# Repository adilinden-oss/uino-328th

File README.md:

## \*uino-328th

The \*uino-328th was designed for my son Mathew. As a mostly though-hole design, it should be easy to assemble even for a beginner.  The only surface mount component is the micro USB connector. Personally I much prefer micro USB over the full sized or mini connector. Unfortunately I was unable to find a through-hole micro USB.  Having the one surface mounted component was a compromise I was willing to take.

The board includes a USB serial bridge based on the PIC16F1454.  Not only is the PIC16F1454 available as a 14 pin though-hole device, it is also considerably less expensive then an ATmega8U2, for example.  

Initially I intend on using the [jgeisler0303/PIC16F1454_USB2Serial](https://github.com/jgeisler0303/PIC16F1454_USB2Serial)  firmware, but ultimately I hope to use the Open Source [signal11/m-stack](https://github.com/signal11/m-stack) as USB serial bridge firmware.

The \*uino-328th is intended to operate at 3.3V.  There are two possible clock sources for the ATmega328P, a dedicated resonator or the clock output of the PIC16F1454.

### Important Note

PCB have been ordered from SeeedStudio FusionPCB service. There is no working sample yet.

### Licensing

This work is licensed under a Creative Commons Attribution-ShareAlike 3.0 Unported License, CC BY-SA.

You are free to copy, distribute and transmit the work. You must attribute the work in the manner specified by the author or licensor (but not in any way that suggests that they endorse you or your use of the work). you alter, transform, or build upon this work, you may distribute the resulting work only under the same or similar license to this one.  

Please refer to [http://creativecommons.org/licenses/by-sa/3.0/] for the license.

### Credit

The \*uino-328th was inspired by:

- The Frienduino [jgeisler0303/Frienduino](https://github.com/jgeisler0303/Frienduino)
- The [Innovation Board](http://make.unl.edu/innovation-board/)

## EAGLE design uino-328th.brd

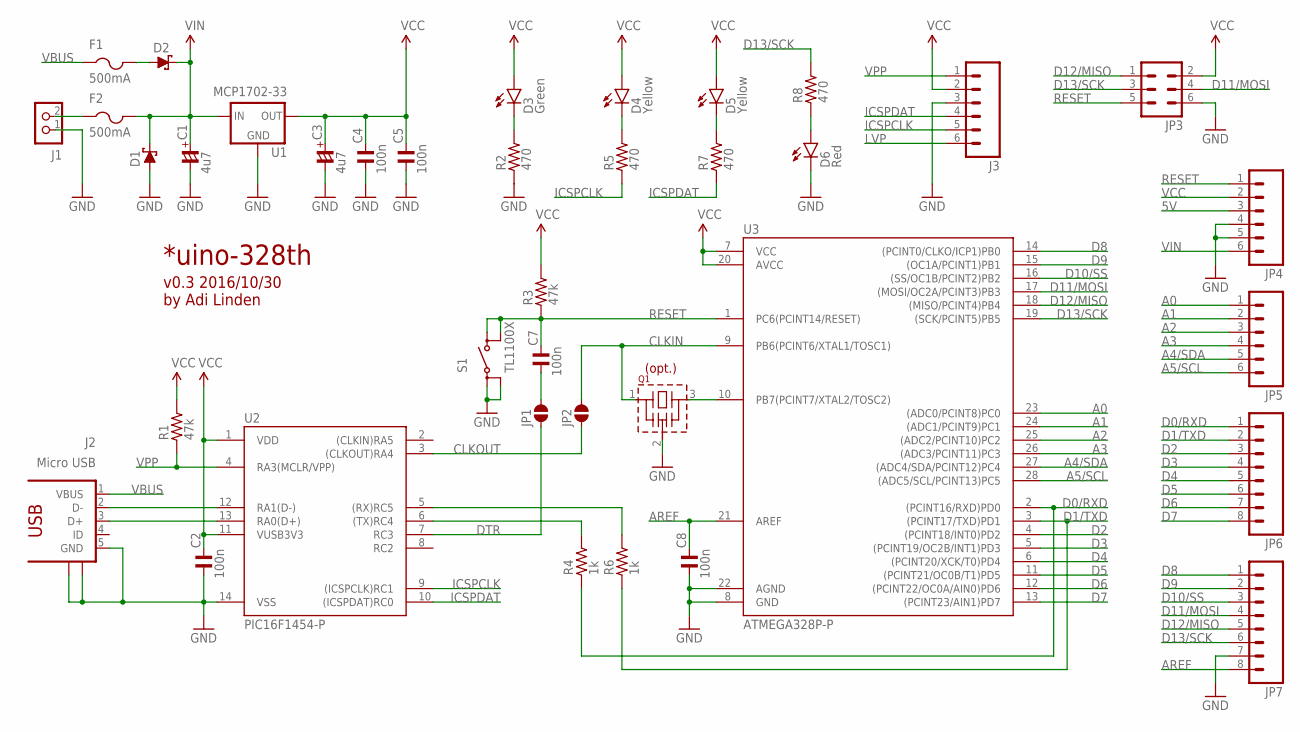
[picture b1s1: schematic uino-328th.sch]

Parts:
C1, C3: 4u7; CTT-025-040
C2, C4, C5, C7, C8: 100n; C025-040X018
D1, D2: SCHOTTKY-DIODEDO35-7; DO35-7
D3: Green; LED3MM
D4, D5: Yellow; LED3MM
D6: Red; LED3MM
F1, F2: 500mA; PTC
J1: CON_TERMINAL_BLOCK_02-5MM; TERMINAL_BLOCK_2P_5
J2: Micro USB; ZX62D-AB-5P8
J3: M06LOCK; 1X06_LOCK
JP1, JP2: SJ-035
JP3: M03X2; 2X03
JP4, JP5: M06SIP; 1X06
JP6, JP7: M081X08; 1X08
Q1: CSTLS_X
R1, R3: 47k; 0207/7
R2, R5, R7: 470; 0207/7
R4, R6: 1k; 0207/10
R8: 470; 0207/10
S1: TL1100X
U1: MCP1702-33; TO-92
U2: PIC16F1454-P; DIL14
U3: ATMEGA328P-P; DIL28-3

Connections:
5V: JP4.3
A0: JP5.1, U3.23 ((ADC0/PCINT8)PC0)
A1: JP5.2, U3.24 ((ADC1/PCINT9)PC1)
A2: JP5.3, U3.25 ((ADC2/PCINT10)PC2)
A3: JP5.4, U3.26 ((ADC3/PCINT11)PC3)
A4/SDA: JP5.5, U3.27 ((ADC4/SDA/PCINT12)PC4)
A5/SCL: JP5.6, U3.28 ((ADC5/SCL/PCINT13)PC5)
AREF: C8.2, JP7.8, U3.21 (AREF)
CLKIN: JP2.2, Q1.1, U3.9 (PB6(PCINT6/XTAL1/TOSC1))
CLKOUT: JP2.1, U2.3 ((CLKOUT)RA4)
D0/RXD: JP6.1, R4.1, U3.2 ((PCINT16/RXD)PD0)
D1/TXD: JP6.2, R6.1, U3.3 ((PCINT17/TXD)PD1)
D2: JP6.3, U3.4 ((PCINT18/INT0)PD2)
D3: JP6.4, U3.5 ((PCINT19/OC2B/INT1)PD3)
D4: JP6.5, U3.6 ((PCINT20/XCK/T0)PD4)
D5: JP6.6, U3.11 ((PCINT21/OC0B/T1)PD5)
D6: JP6.7, U3.12 ((PCINT22/OC0A/AIN0)PD6)
D7: JP6.8, U3.13 ((PCINT23/AIN1)PD7)
D8: JP7.1, U3.14 ((PCINT0/CLKO/ICP1)PB0)
D9: JP7.2, U3.15 ((OC1A/PCINT1)PB1)
D10/SS: JP7.3, U3.16 ((SS/OC1B/PCINT2)PB2)
D11/MOSI: JP3.4, JP7.4, U3.17 ((MOSI/OC2A/PCINT3)PB3)
D12/MISO: JP3.1, JP7.5, U3.18 ((MISO/PCINT4)PB4)
D13/SCK: JP3.3, JP7.6, R8.2, U3.19 ((SCK/PCINT5)PB5)
DTR: JP1.1, U2.7 (RC3)
GND: C1.-, C2.1, C3.-, C4.1, C5.1, C8.1, D1.A, D6.K (C), J1.1, J2.5 (GND), J2.S1, J2.S2, J3.3, JP3.6, JP4.4, JP4.5, JP7.7, Q1.2 (VSS), R2.1, S1.1, S1.2 (P1), U1.1 (GND), U2.14 (VSS), U3.8 (GND), U3.22 (AGND)
ICSPCLK: J3.5, R5.1, U2.9 ((ICSPCLK)RC1)
ICSPDAT: J3.4, R7.1, U2.10 ((ICSPDAT)RC0)
LVP: J3.6
unnamed: D3.K (C), R2.2
unnamed: C7.1, JP1.2
unnamed: J2.2 (D-), U2.12 (RA1(D-))
unnamed: J2.3 (D+), U2.13 (RA0(D+))
unnamed: D6.A, R8.1
unnamed: F2.P$1 (1), J1.2
unnamed: R4.2, U2.6 ((TX)RC4)
unnamed: R6.2, U2.5 ((RX)RC5)
unnamed: Q1.3, U3.10 (PB7(PCINT7/XTAL2/TOSC2))
unnamed: D4.K (C), R5.2
unnamed: D5.K (C), R7.2
unnamed: D2.A, F1.P$2 (2)
RESET: C7.2, JP3.5, JP4.1, R3.1, S1.3 (S), S1.4 (S1), U3.1 (PC6(PCINT14/RESET))
VBUS: F1.P$1 (1), J2.1 (VBUS)
VCC: C2.2, C3.+, C4.2, C5.2, D3.A, D4.A, D5.A, J3.2, JP3.2, JP4.2, R1.2, R3.2, U1.3 (OUT), U2.1 (VDD), U2.11 (VUSB3V3), U3.7 (VCC), U3.20 (AVCC)
VIN: C1.+, D1.C, D2.C, F2.P$2 (2), JP4.6, U1.2 (IN)
VPP: J3.1, R1.1, U2.4 (RA3(MCLR/VPP))

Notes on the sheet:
*uino-328th
v0.3 2016/10/30 by Adi Linden
(opt.)

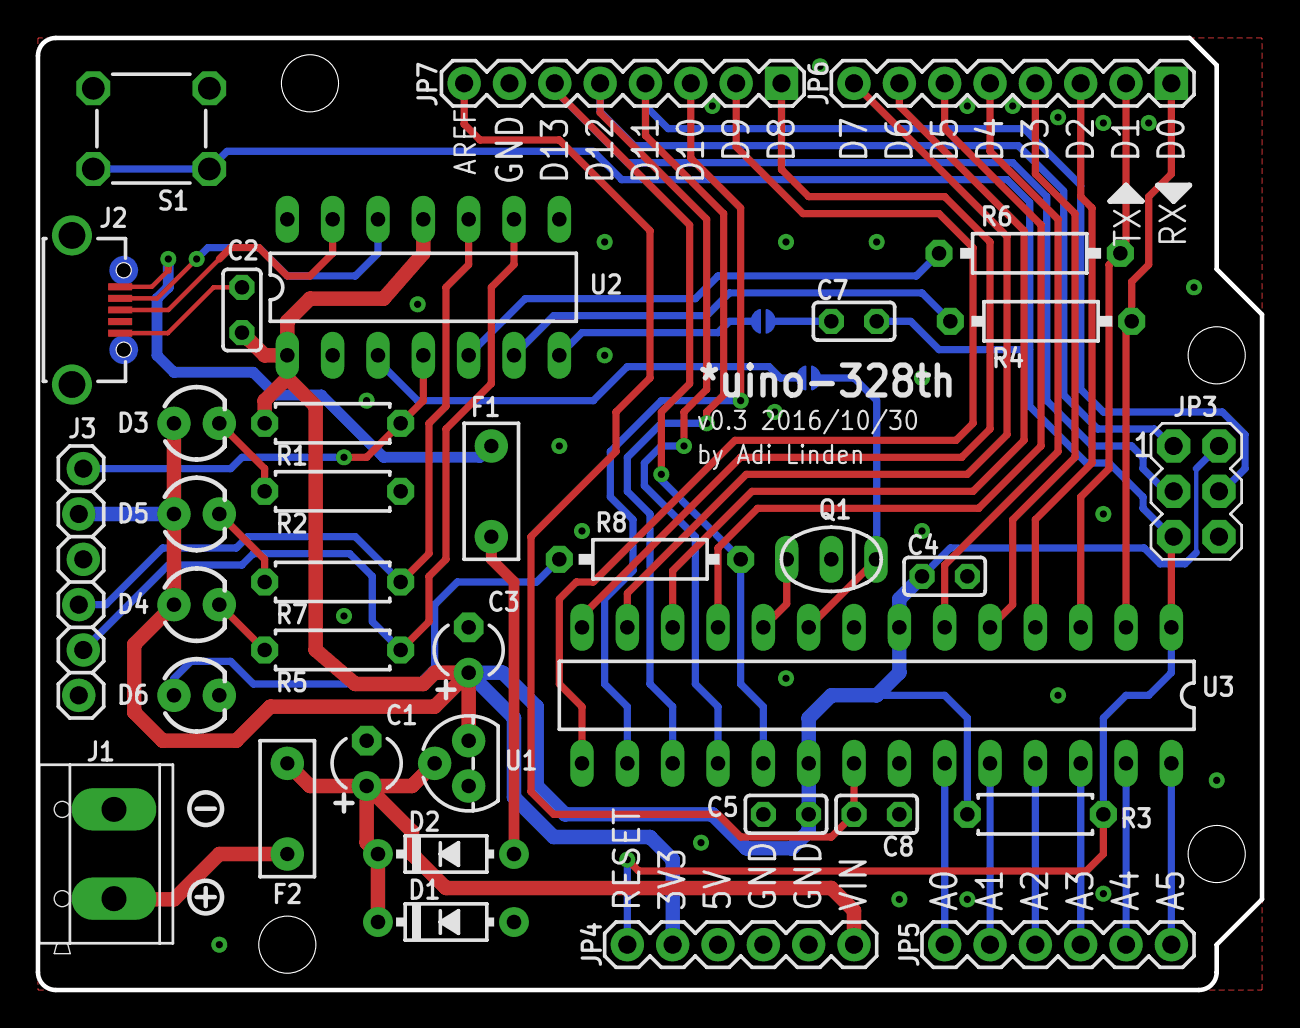
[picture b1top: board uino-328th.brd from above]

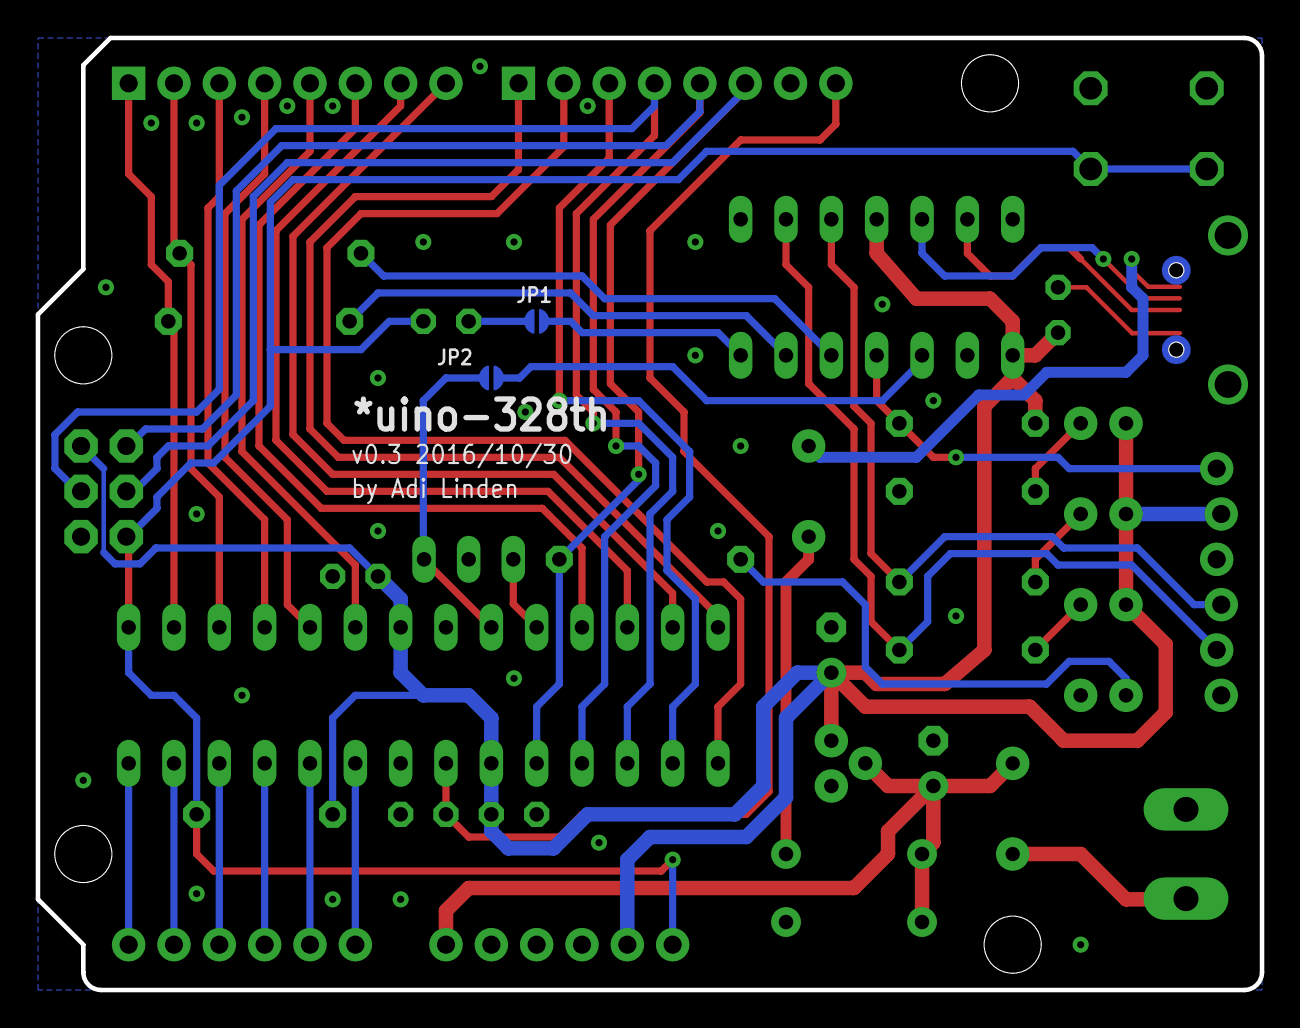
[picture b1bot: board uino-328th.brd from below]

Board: 2 copper layers, 68.6 x 53.3 mm, 38 parts (2 on the bottom side), 44 nets.

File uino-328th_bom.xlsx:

Parts | Qty | Value | Manufacturer Part Number | DigiKey Part Number | Package | Description
C1, C3 | 2 | 4u7 | TAP475M010SCS | 478-8841-ND | 2.5mm | 4.7µF ±20% Conformal Coated Tantalum Capacitors 10V Radial 8 Ohm
C2, C4, C5, C7, C8 | 5 | 100n | K104Z15Y5VF5TL2 | BC1160CT-ND | 2.5mm | 0.10µF -20%, +80% 50V Ceramic Capacitor Y5V (F) Radial
D1, D2 | 2 | 1A | SB140TA | 1655-1514-1-ND | DO-41 | Diode Schottky 40V 1A Through Hole DO-41
D3 | 1 | Green | HLMP1540 | 1080-1046-ND | LED3MM | Green LED Indication - Discrete 2.2V Radial
D4, D5 | 2 | Yellow | 151033YS03000 | 732-5014-ND | LED3MM | Yellow 589nm LED Indication - Discrete 2V Radial
D6 | 1 | Red | 151033RS03000 | 732-5013-ND | LED3MM | Red 621nm LED Indication - Discrete 2V Radial
F1, F2 | 2 | 400mA | 0ZRC0040FF1E | 507-1335-ND | 5mm | PTC Resettable Fuse 90V 400mA Ih Through Hole Radial, Disc
J1 | 1 | CON_TERMINAL_BLOCK_02-5MM | OSTTC022162 | ED2609-ND | 5mm | 2 Position Wire to Board Terminal Block Horizontal with Board 0.200" (5.08mm) T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
J2 | 1 | Micro USB | 475890001 | WM17143CT-ND | ZX62D-AB-5P8 | USB - micro AB Receptacle Connector 5 Position Surface Mount, Right Angle, Hori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
J3 | 1 | Header 1x6 | M20-9990645 | 952-2269-ND | 1X06 | 6 Positions Header, Unshrouded, Breakaway Connector 0.100" (2.54mm) Through Hol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
JP3 | 1 | Header 2x3 | M20-9980345 | 952-2120-ND | 2X03 | 6 Positions Header, Unshrouded, Breakaway Connector 0.100" (2.54mm) Through Hol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
JP4, JP5 | 2 | Header 1x6 | PPTC061LFBN-RC | S7004-ND | 1X06 | 6 Position Header Connector 0.100" (2.54mm) Through Hole Tin
JP6, JP7 | 2 | Header 1x8 | PPTC081LFBN-RC | S7006-ND | 1X08 | 8 Position Header Connector 0.100" (2.54mm) Through Hole Tin
Q1 | 1 | 12MHz | AWCR-12.00RS | 535-13413-ND | CSTLS_X | 12MHz Ceramic Resonator Built in Capacitor 15pF ±0.5% 25 Ohm -25°C ~ 85°C Throu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
R1, R3 | 2 | 47k | CF14JT47K0 | CF14JT47K0CT-ND | 0207/7 | RES 47K OHM 1/4W 5% CARBON FILM
R2, R5, R7,R8 | 3 | 470 | CF14JT470R | CF14JT470RCT-ND | 0207/7 | RES 470 OHM 1/4W 5% CARBON FILM
R4, R6 | 2 | 1k | CF14JT1K00 | CF14JT1K00CT-ND | 0207/10 | RES 1K OHM 1/4W 5% CARBON FILM
S1 | 1 | Tactile Switch | 1825910-6 | 450-1650-ND | TL1100X | Tactile Switch SPST-NO Top Actuated Through Hole
U1 | 1 | MCP1702-33 | MCP1702-3302E/TO | MCP1702-3302E/TO-ND | TO-92 | Linear Voltage Regulator IC Positive Fixed 1 Output 3.3V 250mA TO-92-3
U2 | 1 | PIC16F1454-I/P | PIC16F1454-I/P | PIC16F1454-I/P-ND | DIL14 | PIC PIC® XLP™ 16F Microcontroller IC 8-Bit 48MHz 14KB (8K x 14) FLASH 14-PDIP
U3 | 1 | ATMEGA328P-PU | ATMEGA328P-PU | ATMEGA328P-PU-ND | DIL28-3 | AVR AVR® ATmega Microcontroller IC 8-Bit 20MHz 32KB (16K x 16) FLASH 28-PDIP

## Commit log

2016-10-24 Added new project.
2016-10-25 Schematic complete.
2016-10-26 Changed to 3V3 and 5V hybrid.
2016-10-27 Attempts at routing board.
2016-10-30 First cut to try gerber.
2016-10-31 Created/updated Eagle project. Added .gitignore.
2016-10-31 Some minor final changes.
2016-10-31 Ran cam jon to create gerber.
2016-11-04 Added values. Added png files.
2016-11-04 Added README.md.
2016-11-04 Fixed typo.
2016-11-14 Added BOM.
2016-11-14 Created gerber for SeeedStudio FusionPCB order.
2019-02-22 Fixed formatting.

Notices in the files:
parts and their libraries:
rc-master-th: Copyright (C) 2007-2008, Bob Starr
SparkFun-Connectors: Licensing: Creative Commons ShareAlike 4.0 International - https://creativecommons.org/licenses/by-sa/4.0
jumpers: Copyright (C) 2009, Bob Starr
